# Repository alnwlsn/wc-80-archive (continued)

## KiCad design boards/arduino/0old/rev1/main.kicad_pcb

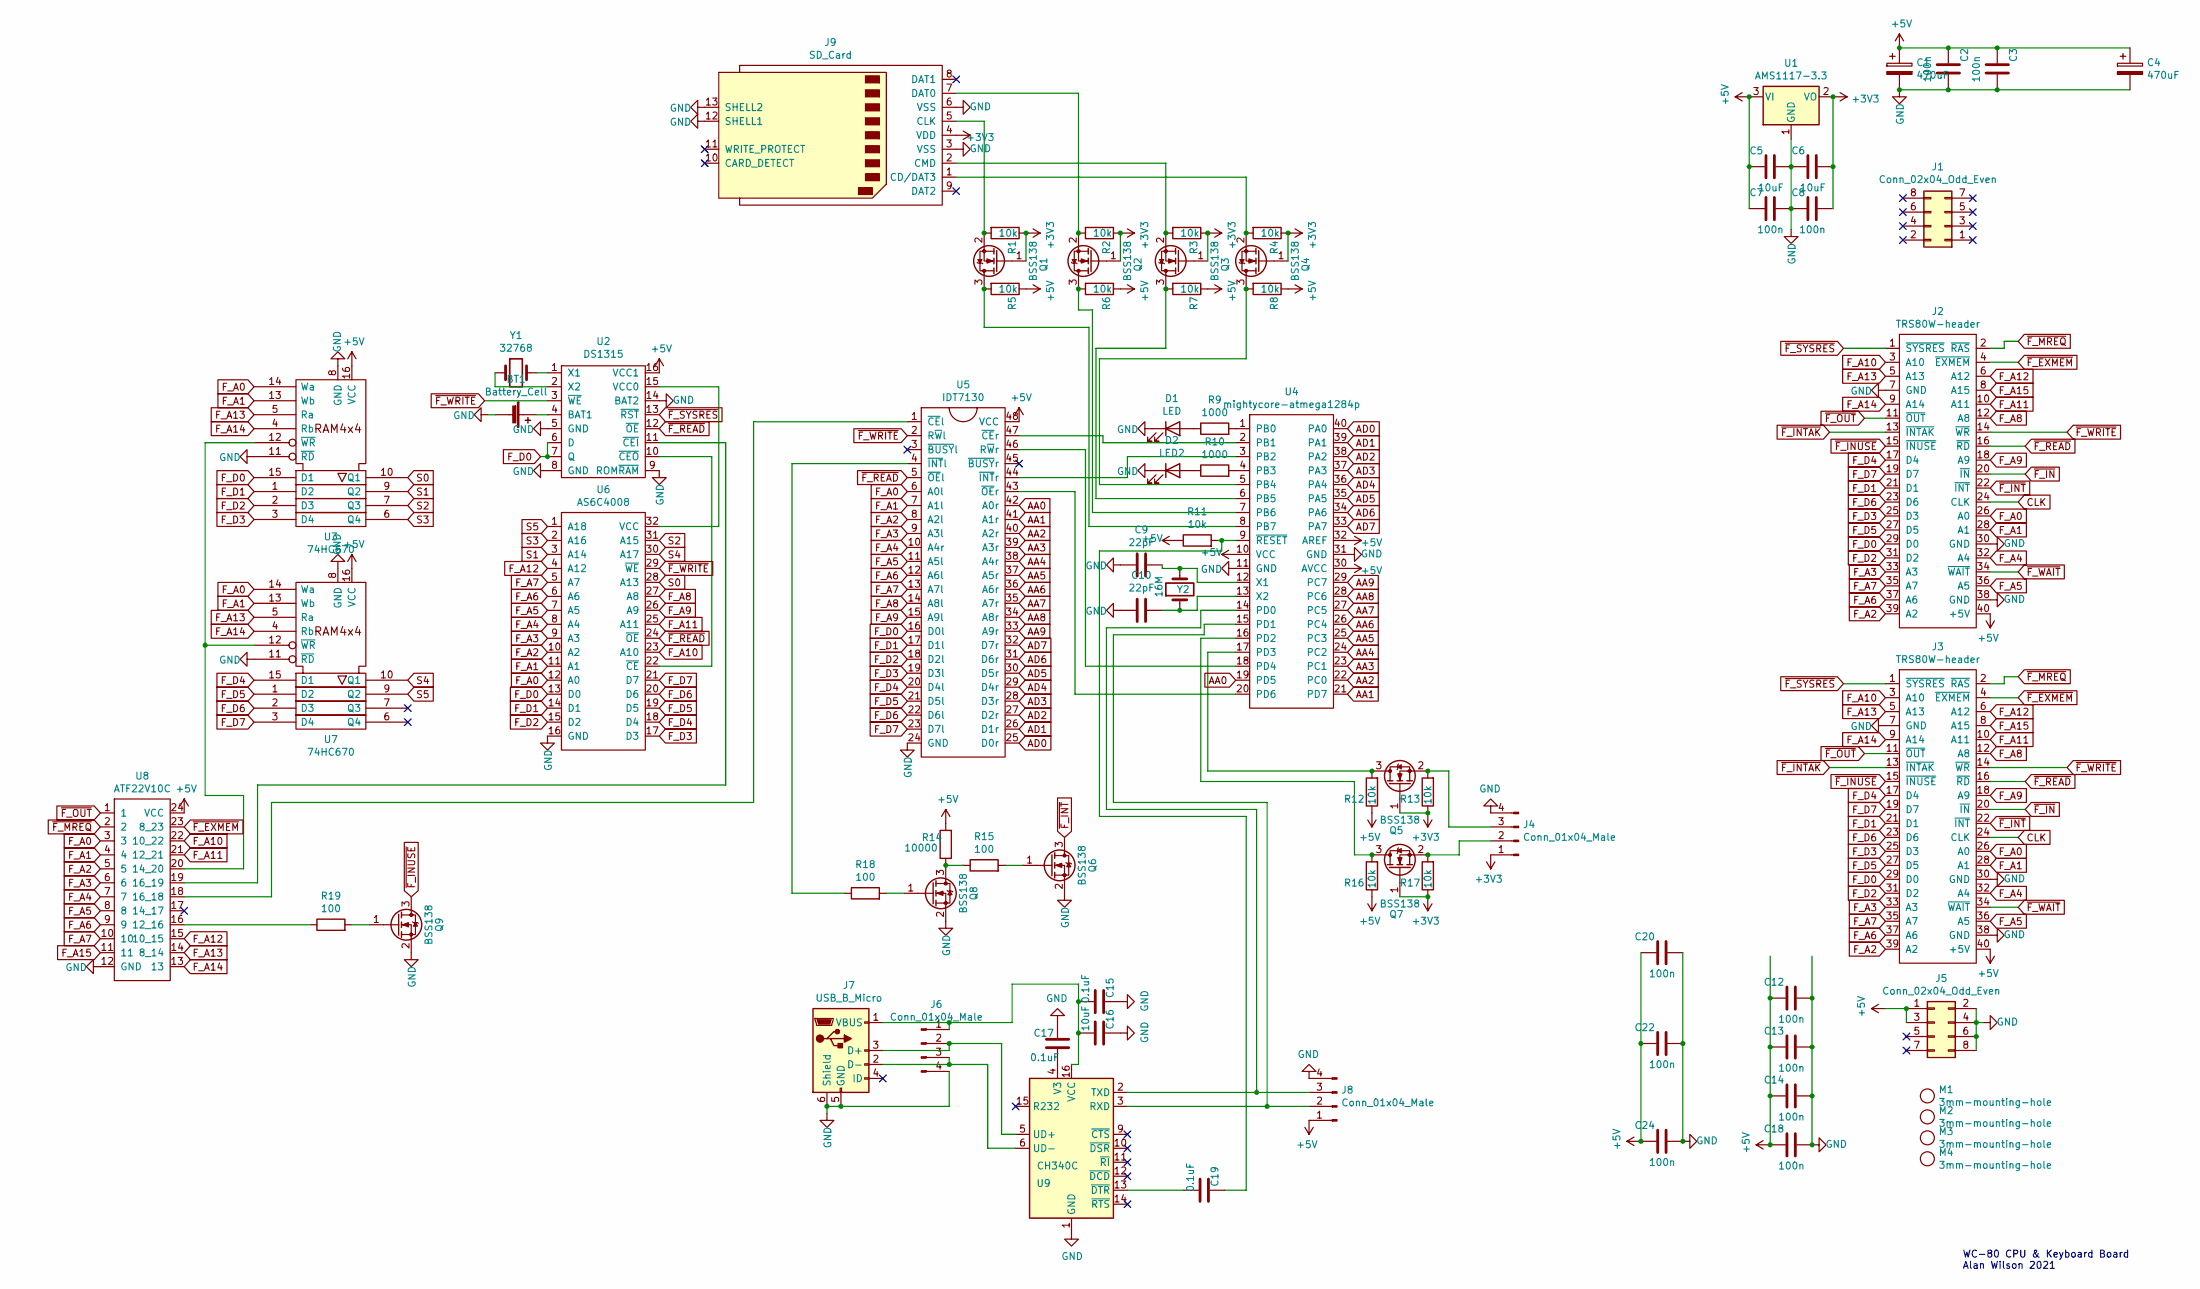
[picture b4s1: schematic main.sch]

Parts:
BT1: Battery_Cell; BS-01-A4CJ004
C1, C4: 470uF; CP_Radial_D8.0mm_P3.50mm
C2, C3, C7, C8, C12, C13, C14, C18, C20, C22, C24: 100n; C_0805_2012Metric
C5, C6, C16: 10uF; C_0805_2012Metric
C9, C10: 22pF; C_0805_2012Metric
C15, C17, C19: 0.1uF; C_0805_2012Metric
D1: LED; LED_D3.0mm
D2: LED2; LED_D3.0mm
J1, J5: Conn_02x04_Odd_Even; PinHeader_2x04_P2.54mm_Vertical
J2, J3: TRS80W-header; PinHeader_2x20_P2.54mm_Vertical
J4, J6, J8: Conn_01x04_Male; PinHeader_1x04_P2.54mm_Vertical
J7: USB_B_Micro; USB_Micro-B_Molex-105017-0001
J9: SD_Card; SD_Card_ XUNPU_SD-101
M1, M2, M3, M4: 3mm-mounting-hole; MountingHole_3.2mm_M3_DIN965
Q1, Q2, Q3, Q4, Q5, Q6, Q7, Q8, Q9: BSS138; SOT-23
R1, R2, R3, R4, R5, R6, R7, R8, R11, R12, R13, R16, R17: 10k; R_0805_2012Metric
R9, R10: 1000; R_0805_2012Metric
R14: 10000; R_0805_2012Metric
R15, R18, R19: 100; R_0805_2012Metric
U1: AMS1117-3.3; SOT-223-3_TabPin2
U2: DS1315; DIP-16_W7.62mm_Socket
U3, U7: 74HC670; DIP-16_W7.62mm_Socket
U4: mightycore-atmega1284p; DIP-40_W15.24mm_Socket
U5: IDT7130; DIP-48_W15.24mm_Socket
U6: AS6C4008; DIP-32_W15.24mm
U8: ATF22V10C; DIP-24_W7.62mm
U9: CH340C; SOIC-16_3.9x9.9mm_P1.27mm
Y1: 32768; Crystal_AT310_D3.0mm_L10.0mm_Horizontal
Y2: 16M; Crystal_HC49-U_Vertical

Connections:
+3V3: C6.2, C8.2, J4.1, J9.4 (VDD), Q1.1 (G), Q2.1 (G), Q3.1 (G), Q4.1 (G), Q5.1 (G), Q7.1 (G), R1.1, R2.1, R3.1, R4.1, R13.1, R17.1, U1.2 (VO)
+5V: C1.1, C2.1, C3.1, C4.1, C5.1, C7.1, C12.1, C13.1, C14.1, C18.1, C20.1, C22.1, C24.1, J2.40 (+5V), J3.40 (+5V), J5.1, J5.3, J8.1, R5.1, R6.1, R7.1, R8.1, R11.1, R12.1, R14.2, R16.1, U1.3 (VI), U2.16 (VCC1), U3.16 (VCC), U4.10 (VCC), U4.30 (AVCC), U4.32 (AREF), U5.48 (VCC), U7.16 (VCC), U8.24 (VCC)
AA0: U4.19 (PD5), U5.42 (A0r)
AA1: U4.21 (PD7), U5.41 (A1r)
AA2: U4.22 (PC0), U5.40 (A2r)
AA3: U4.23 (PC1), U5.39 (A3r)
AA4: U4.24 (PC2), U5.38 (A4r)
AA5: U4.25 (PC3), U5.37 (A5r)
AA6: U4.26 (PC4), U5.36 (A6r)
AA7: U4.27 (PC5), U5.35 (A7r)
AA8: U4.28 (PC6), U5.34 (A8r)
AA9: U4.29 (PC7), U5.33 (A9r)
AD0: U4.40 (PA0), U5.25 (D0r)
AD1: U4.39 (PA1), U5.26 (D1r)
AD2: U4.38 (PA2), U5.27 (D2r)
AD3: U4.37 (PA3), U5.28 (D3r)
AD4: U4.36 (PA4), U5.29 (D4r)
AD5: U4.35 (PA5), U5.30 (D5r)
AD6: U4.34 (PA6), U5.31 (D6r)
AD7: U4.33 (PA7), U5.32 (D7r)
CLK: J2.24 (CLK), J3.24 (CLK)
F_A0: J2.26 (A0), J3.26 (A0), U3.14 (Wa), U5.6 (A0l), U6.12 (A0), U7.14 (Wa), U8.3
F_A1: J2.28 (A1), J3.28 (A1), U3.13 (Wb), U5.7 (A1l), U6.11 (A1), U7.13 (Wb), U8.4
F_A2: J2.39 (A2), J3.39 (A2), U5.8 (A2l), U6.10 (A2), U8.5
F_A3: J2.33 (A3), J3.33 (A3), U5.9 (A3l), U6.9 (A3), U8.6
F_A4: J2.32 (A4), J3.32 (A4), U5.10 (A4r), U6.8 (A4), U8.7
F_A5: J2.36 (A5), J3.36 (A5), U5.11 (A5l), U6.7 (A5), U8.8
F_A6: J2.37 (A6), J3.37 (A6), U5.12 (A6l), U6.6 (A6), U8.9
F_A7: J2.35 (A7), J3.35 (A7), U5.13 (A7l), U6.5 (A7), U8.10
F_A8: J2.12 (A8), J3.12 (A8), U5.14 (A8l), U6.27 (A8)
F_A9: J2.18 (A9), J3.18 (A9), U5.15 (A9l), U6.26 (A9)
F_A10: J2.3 (A10), J3.3 (A10), U6.23 (A10), U8.22 (10_22)
F_A11: J2.10 (A11), J3.10 (A11), U6.25 (A11), U8.21 (12_21)
F_A12: J2.6 (A12), J3.6 (A12), U6.4 (A12), U8.15 (10_15)
F_A13: J2.5 (A13), J3.5 (A13), U3.5 (Ra), U7.5 (Ra), U8.14 (8_14)
F_A14: J2.9 (A14), J3.9 (A14), U3.4 (Rb), U7.4 (Rb), U8.13
F_A15: J2.8 (A15), J3.8 (A15), U8.11
F_D0: J2.29 (D0), J3.29 (D0), U2.6 (D), U2.7 (Q), U3.15 (D1), U5.16 (D0l), U6.13 (D0)
F_D1: J2.21 (D1), J3.21 (D1), U3.1 (D2), U5.17 (D1l), U6.14 (D1)
F_D2: J2.31 (D2), J3.31 (D2), U3.2 (D3), U5.18 (D2l), U6.15 (D2)
F_D3: J2.25 (D3), J3.25 (D3), U3.3 (D4), U5.19 (D3l), U6.17 (D3)
F_D4: J2.17 (D4), J3.17 (D4), U5.20 (D4l), U6.18 (D4), U7.15 (D1)
F_D5: J2.27 (D5), J3.27 (D5), U5.21 (D5l), U6.19 (D5), U7.1 (D2)
F_D6: J2.23 (D6), J3.23 (D6), U5.22 (D6l), U6.20 (D6), U7.2 (D3)
F_D7: J2.19 (D7), J3.19 (D7), U5.23 (D7l), U6.21 (D7), U7.3 (D4)
GND: BT1.2 (-), C1.2, C2.2, C3.2, C4.2, C5.2, C6.1, C7.2, C8.1, C9.2, C10.2, C12.2, C13.2, C14.2, C15.2, C16.2, C17.2, C18.2, C20.2, C22.2, C24.2, D1.1 (K), D2.1 (K), J2.7 (GND), J2.30 (GND), J2.38 (GND), J3.7 (GND), J3.30 (GND), J3.38 (GND), J4.4, J5.2, J5.4, J5.6, J5.8, J6.4, J7.5 (GND), J7.6 (Shield), J8.4, J9.3 (VSS), J9.6 (VSS), J9.12 (SHELL1), J9.13 (SHELL2), Q6.2 (S), Q8.2 (S), Q9.2 (S), U1.1 (GND), U2.5 (GND), U2.8 (GND), U2.9 (ROM~RAM~), U2.14 (BAT2), U3.8 (GND), U3.11 (~RD), U4.11 (GND), U4.31 (GND), U5.24 (GND), U6.16 (GND), U7.8 (GND), U7.11 (~RD), U8.12 (GND), U9.1 (GND)
unnamed: BT1.1 (+), U2.4 (BAT1)
unnamed: C9.1, U4.12 (X1), Y2.2
unnamed: C10.1, U4.13 (X2), Y2.1
unnamed: C15.1, C16.1, J6.1, J7.1 (VBUS), U9.16 (VCC)
unnamed: C17.1, U9.4 (V3)
unnamed: C19.1, U9.13 (~DTR)
unnamed: C19.2, R11.2, U4.9 (~RESET~)
unnamed: D1.2 (A), R9.1
unnamed: D2.2 (A), R10.1
unnamed: J4.2, Q7.2 (S), R17.2
unnamed: J4.3, Q5.2 (S), R13.2
unnamed: J6.2, J7.3 (D+), U9.5 (UD+)
unnamed: J6.3, J7.2 (D-), U9.6 (UD-)
unnamed: J8.2, U4.15 (PD1), U9.3 (RXD)
unnamed: J8.3, U4.14 (PD0), U9.2 (TXD)
unnamed: J9.1 (CD/DAT3), Q4.2 (S), R4.2
unnamed: J9.2 (CMD), Q3.2 (S), R3.2
unnamed: J9.5 (CLK), Q1.2 (S), R1.2
unnamed: J9.7 (DAT0), Q2.2 (S), R2.2
unnamed: Q1.3 (D), R5.2, U4.8 (PB7)
unnamed: Q2.3 (D), R6.2, U4.7 (PB6)
unnamed: Q3.3 (D), R7.2, U4.6 (PB5)
unnamed: Q4.3 (D), R8.2, U4.5 (PB4)
unnamed: Q5.3 (D), R12.2, U4.17 (PD3)
unnamed: Q6.1 (G), R15.2
unnamed: Q7.3 (D), R16.2, U4.16 (PD2)
unnamed: Q8.1 (G), R18.2
unnamed: Q8.3 (D), R14.1, R15.1
unnamed: Q9.1 (G), R19.2
unnamed: R9.2, U4.1 (PB0)
unnamed: R10.2, U4.4 (PB3)
unnamed: R18.1, U5.4 (~INT~l)
unnamed: R19.1, U8.16 (12_16)
unnamed: U2.1 (X1), Y1.2
unnamed: U2.2 (X2), Y1.1
unnamed: U2.10 (~CEO~), U6.22 (~CE~)
unnamed: U2.11 (~CEI~), U8.19 (16_19)
unnamed: U2.15 (VCC0), U6.32 (VCC)
unnamed: U3.12 (~WR), U7.12 (~WR), U8.20 (14_20)
unnamed: U4.2 (PB1), U5.47 (~CE~r)
unnamed: U4.3 (PB2), U5.44 (~INT~r)
unnamed: U4.18 (PD4), U5.46 (R~W~r)
unnamed: U4.20 (PD6), U5.43 (~OE~r)
unnamed: U5.1 (~CE~l), U8.18 (16_18)
S0: U3.10 (Q1), U6.28 (A13)
S1: U3.9 (Q2), U6.3 (A14)
S2: U3.7 (Q3), U6.31 (A15)
S3: U3.6 (Q4), U6.2 (A16)
S4: U6.30 (A17), U7.10 (Q1)
S5: U6.1 (A18), U7.9 (Q2)
~F_EXMEM~: J2.4 (~EXMEM~), J3.4 (~EXMEM~), U8.23 (8_23)
~F_INTAK~: J2.13 (~INTAK~), J3.13 (~INTAK~)
~F_INT~: J2.22 (~INT~), J3.22 (~INT~), Q6.3 (D)
~F_INUSE~: J2.15 (~INUSE~), J3.15 (~INUSE~), Q9.3 (D)
~F_IN~: J2.20 (~IN~), J3.20 (~IN~)
~F_MREQ~: J2.2 (~RAS~), J3.2 (~RAS~), U8.2
~F_OUT~: J2.11 (~OUT~), J3.11 (~OUT~), U8.1
~F_READ~: J2.16 (~RD~), J3.16 (~RD~), U2.12 (~OE~), U5.5 (~OE~l), U6.24 (~OE~)
~F_SYSRES~: J2.1 (~SYSRES~), J3.1 (~SYSRES~), U2.13 (~RST~)
~F_WAIT~: J2.34 (~WAIT~), J3.34 (~WAIT~)
~F_WRITE~: J2.14 (~WR~), J3.14 (~WR~), U2.3 (~WE~), U5.2 (R~W~l), U6.29 (~WE~)

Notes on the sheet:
WC-80 CPU & Keyboard Board Alan Wilson 2021

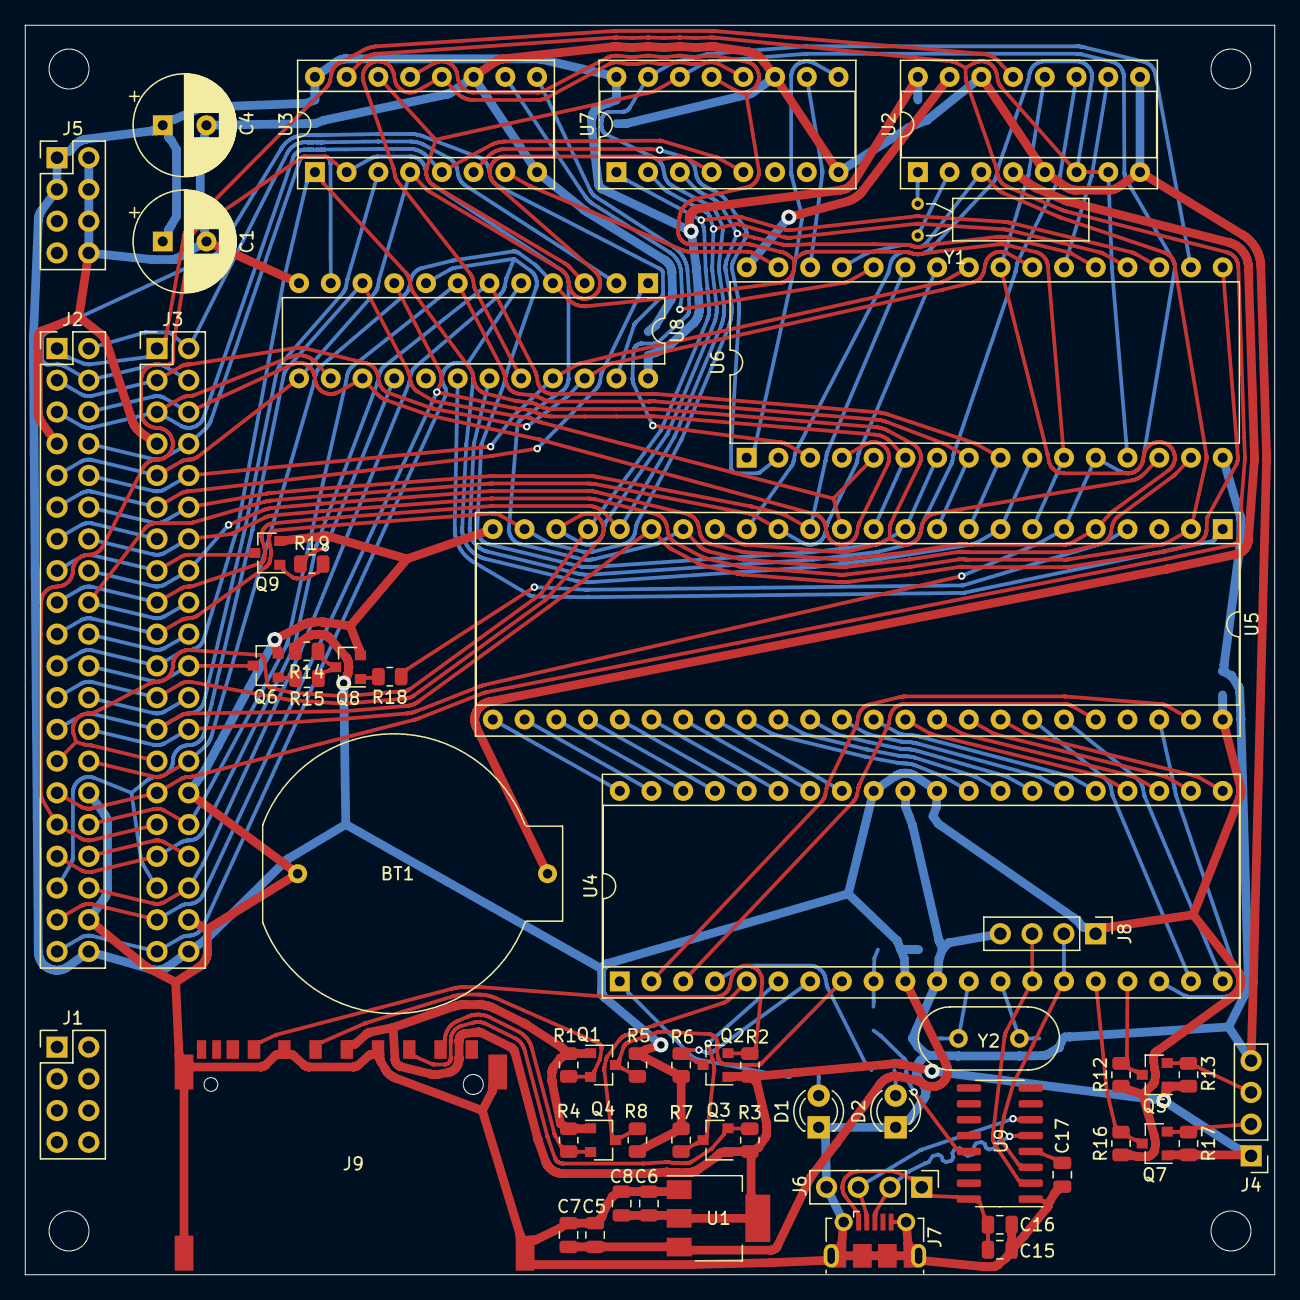
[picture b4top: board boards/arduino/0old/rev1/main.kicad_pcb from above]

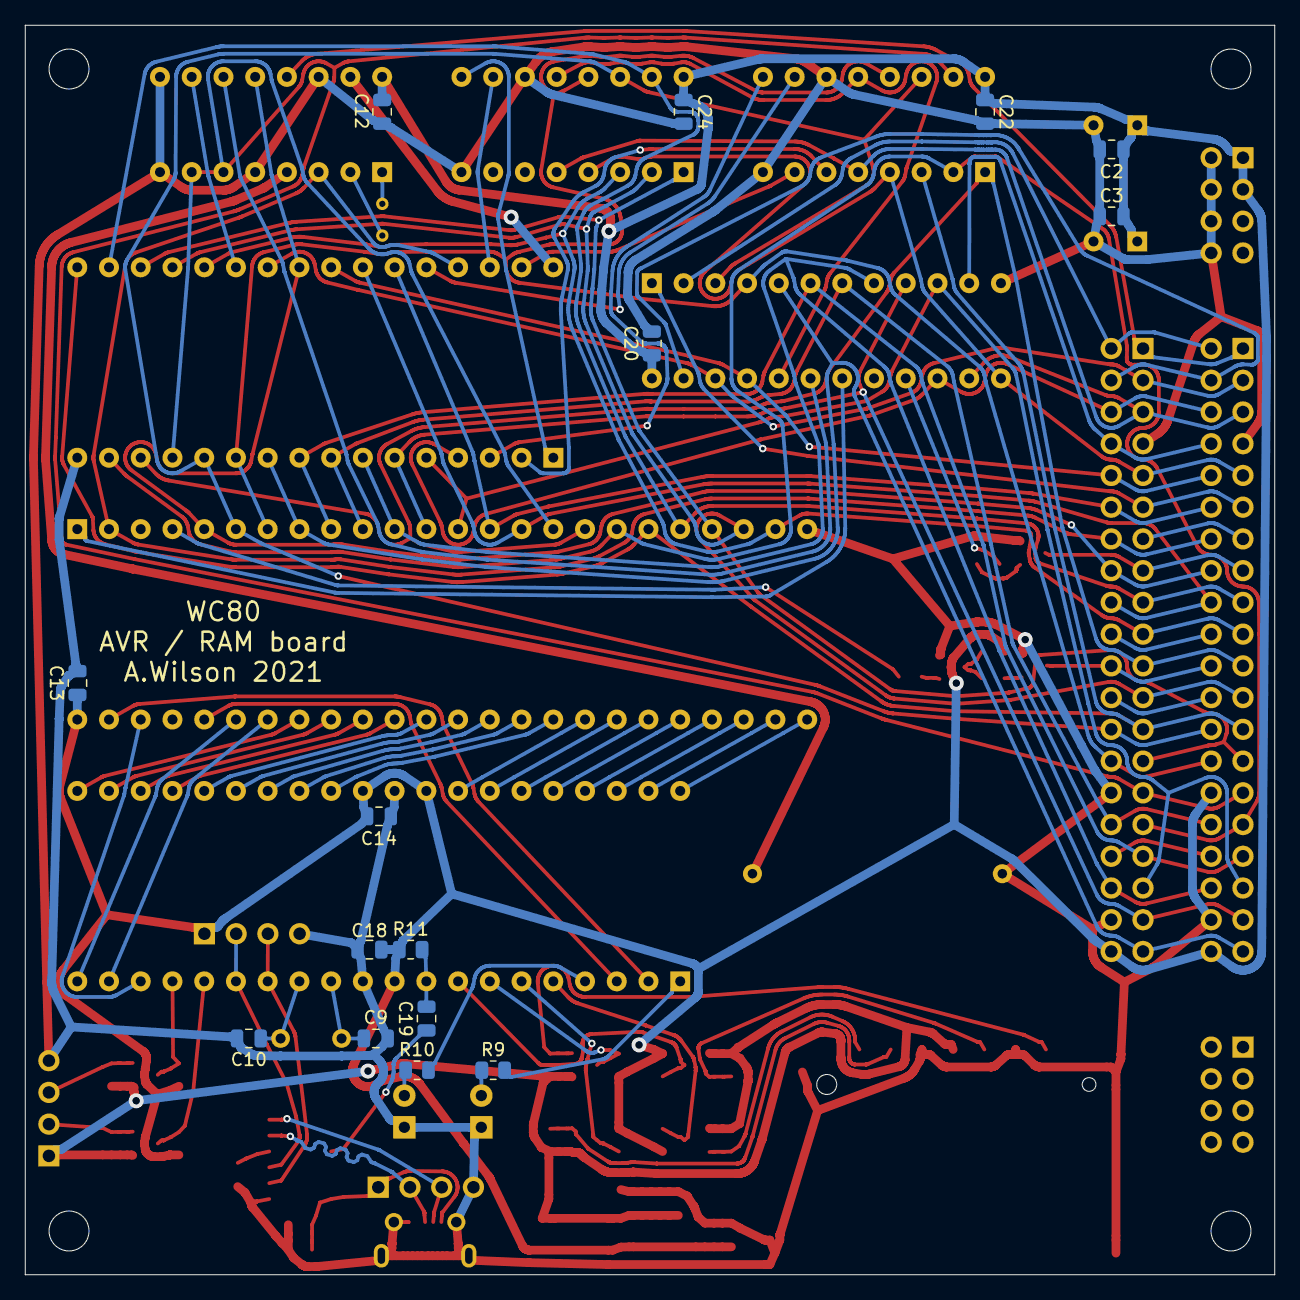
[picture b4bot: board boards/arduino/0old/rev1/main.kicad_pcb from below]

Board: 2 copper layers, 100.0 x 100.0 mm, 76 parts (15 on the bottom side), 107 nets.

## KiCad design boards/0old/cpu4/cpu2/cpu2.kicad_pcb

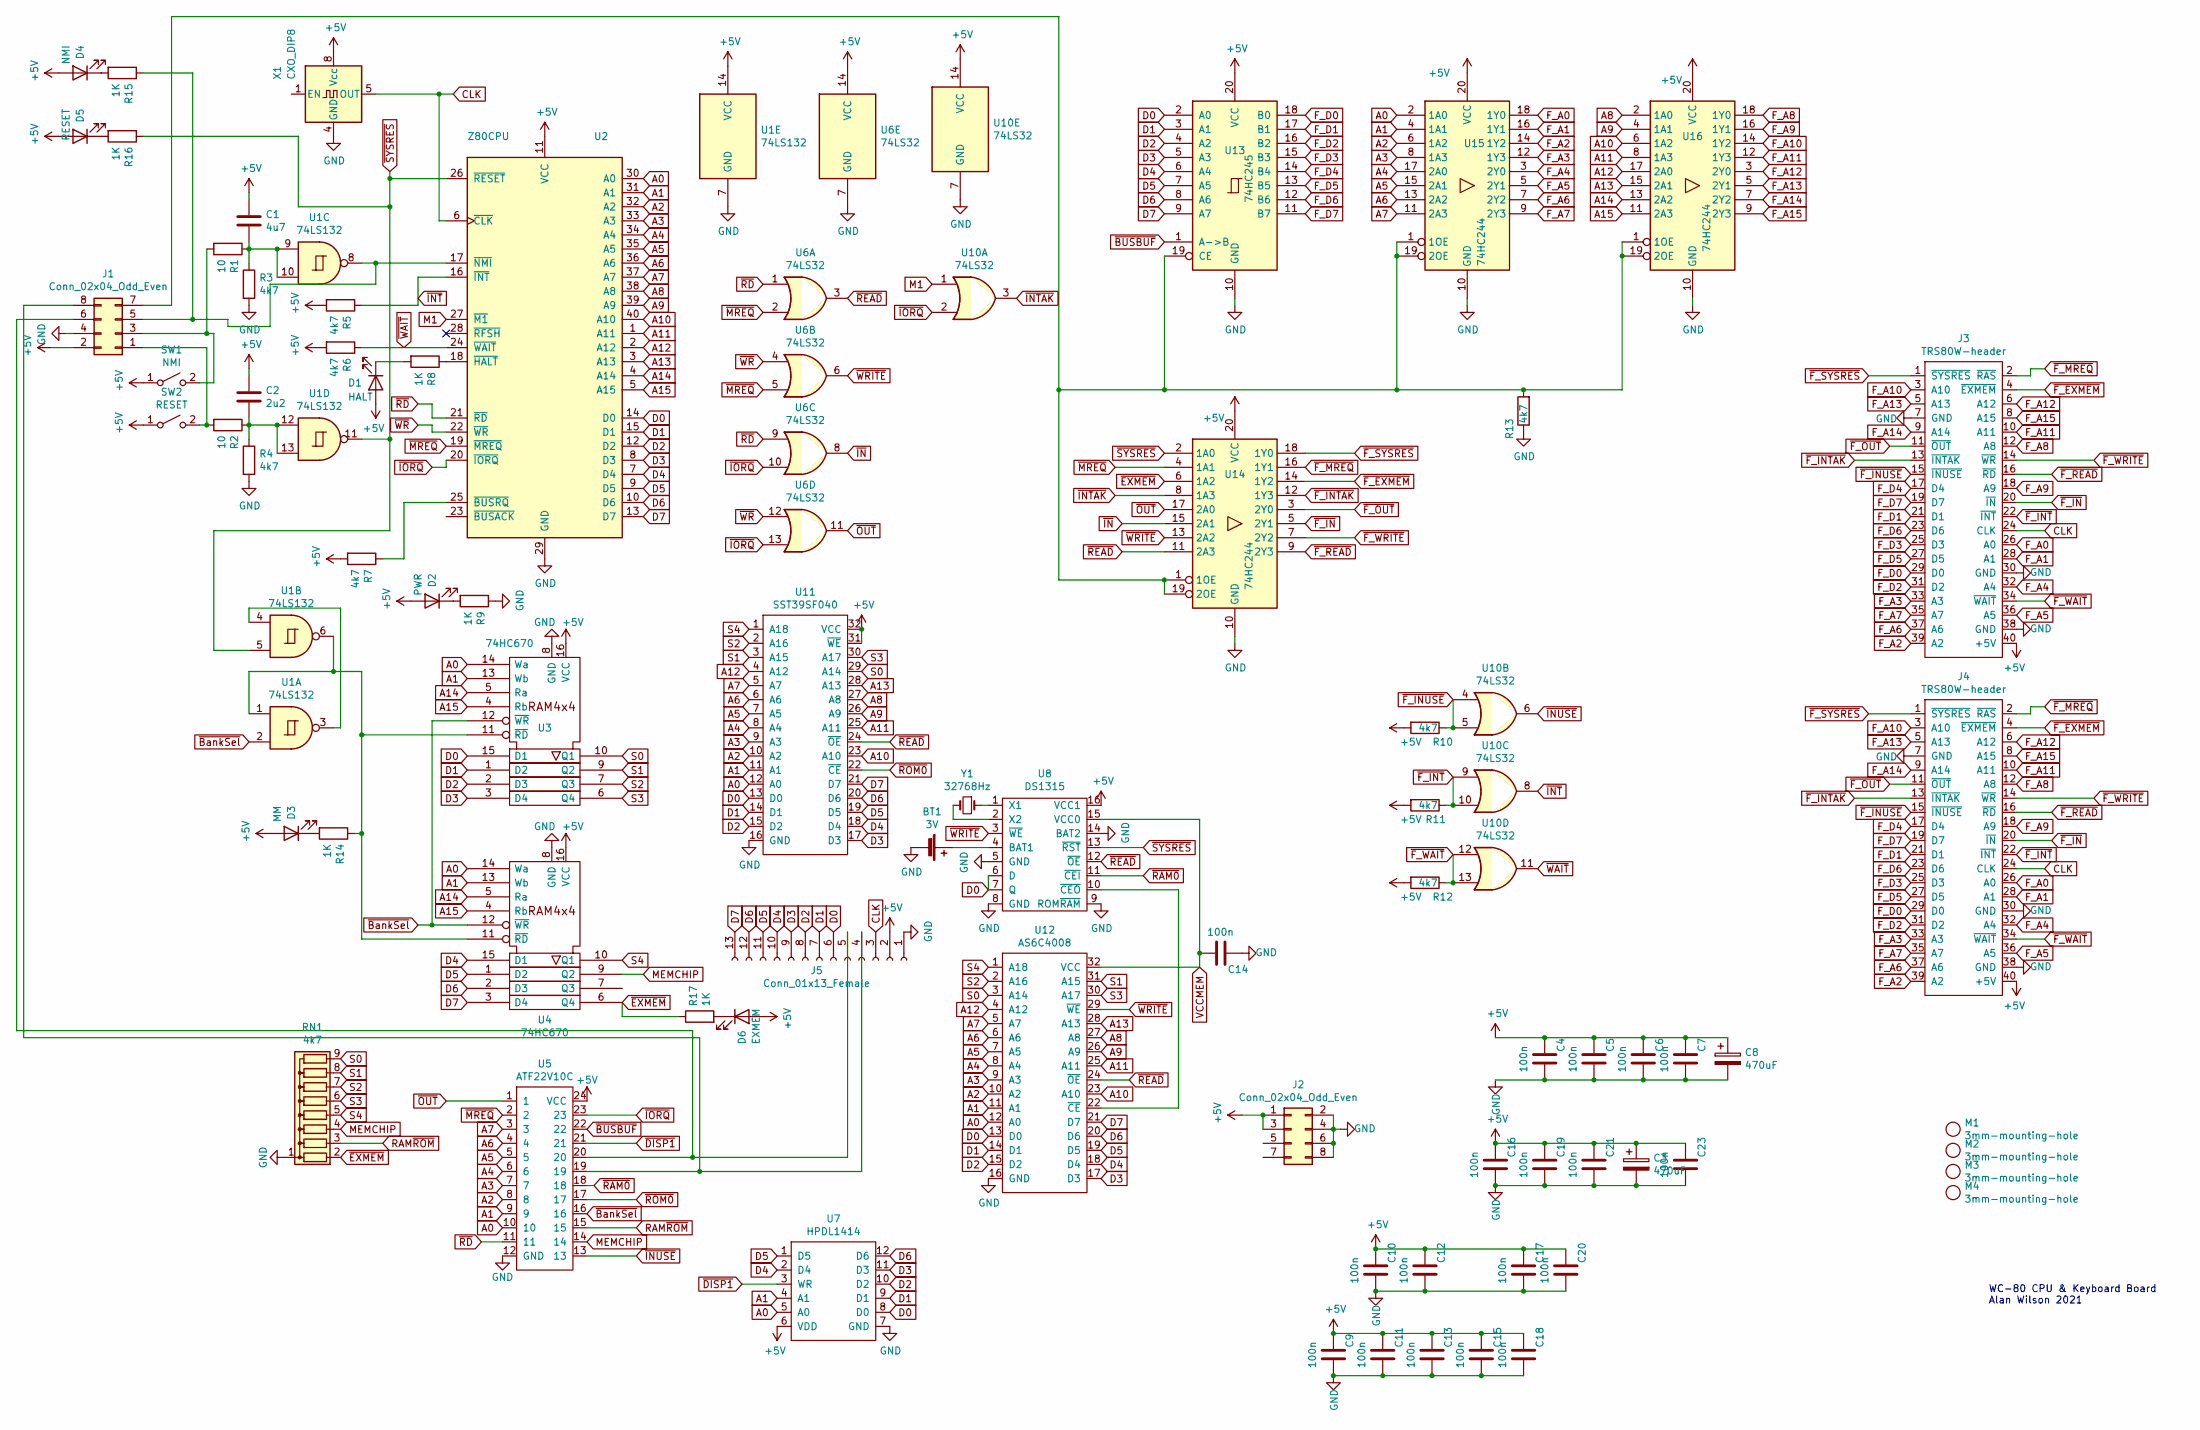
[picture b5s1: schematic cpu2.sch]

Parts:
BT1: 3V; BS-01-A4CJ004
C1: 4u7; C_0805_2012Metric
C2: 2u2; C_0805_2012Metric
C3, C8: 470uF; CP_Radial_D8.0mm_P3.50mm
C4, C5, C6, C7, C9, C10, C11, C12, C13, C14, C15, C16, C17, C18, C19, C20, C21, C23: 100n; C_0805_2012Metric
D1: HALT; LED_D3.0mm_FlatTop
D2: PWR; LED_D3.0mm_FlatTop
D3: MM; LED_D3.0mm_FlatTop
D4: NMI; LED_D3.0mm_FlatTop
D5: RESET; LED_D3.0mm_FlatTop
D6: EXMEM; LED_D3.0mm_FlatTop
J1, J2: Conn_02x04_Odd_Even; PinHeader_2x04_P2.54mm_Vertical
J3, J4: TRS80W-header; PinHeader_2x20_P2.54mm_Vertical
J5: Conn_01x13_Female; PinHeader_1x13_P2.54mm_Vertical
M1, M2, M3, M4: 3mm-mounting-hole; MountingHole_3.2mm_M3_DIN965_Pad
R1, R2: 10; R_0805_2012Metric
R3, R4, R5, R6, R7, R10, R11, R12, R13: 4k7; R_0805_2012Metric
R8, R9, R14, R15, R16, R17: 1K; R_0805_2012Metric
RN1: 4k7; R_Array_SIP9
SW1: NMI; SW_PUSH_6mm
SW2: RESET; SW_PUSH_6mm
U1: 74LS132; DIP-14_W7.62mm_Socket
U2: Z80CPU; DIP-40_W15.24mm_Socket
U3, U4: 74HC670; DIP-16_W7.62mm_Socket
U5: ATF22V10C; DIP-24_W7.62mm_Socket
U6, U10: 74LS32; DIP-14_W7.62mm_Socket
U7: HPDL1414; DIP-24_W15.24mm_Socket
U8: DS1315; DIP-16_W7.62mm_Socket
U11: SST39SF040; DIP-32_W15.24mm_Socket
U12: AS6C4008; DIP-32_W15.24mm_Socket
U13: 74HC245; DIP-20_W7.62mm_Socket
U14, U15, U16: 74HC244; DIP-20_W7.62mm_Socket
X1: CXO_DIP8; Oscillator_DIP-8
Y1: 32768Hz; Crystal_AT310_D3.0mm_L10.0mm_Horizontal

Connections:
+5V: C1.1, C2.1, C3.1, C4.1, C5.1, C6.1, C7.1, C8.1, C9.1, C10.1, C11.1, C12.1, C13.1, C15.1, C16.1, C17.1, C18.1, C19.1, C20.1, C21.1, C23.1, D1.2 (A), D2.2 (A), D3.2 (A), D4.2 (A), D5.2 (A), D6.2 (A), J1.2, J2.1, J2.3, J3.40 (+5V), J4.40 (+5V), J5.2, R5.2, R6.2, R7.2, R10.2, R11.2, R12.2, SW1.1 (A), SW2.1 (A), U1.14 (VCC), U2.11 (VCC), U3.16 (VCC), U4.16 (VCC), U5.24 (VCC), U6.14 (VCC), U7.6 (VDD), U8.16 (VCC1), U10.14 (VCC), U11.31 (~WE~), U11.32 (VCC), U13.20 (VCC), U14.20 (VCC), U15.20 (VCC), U16.20 (VCC), X1.8 (Vcc)
A0: U2.30 (A0), U3.14 (Wa), U4.14 (Wa), U5.10, U7.5 (A0), U11.12 (A0), U12.12 (A0), U15.2 (1A0)
A1: U2.31 (A1), U3.13 (Wb), U4.13 (Wb), U5.9, U7.4 (A1), U11.11 (A1), U12.11 (A1), U15.4 (1A1)
A2: U2.32 (A2), U5.8, U11.10 (A2), U12.10 (A2), U15.6 (1A2)
A3: U2.33 (A3), U5.7, U11.9 (A3), U12.9 (A3), U15.8 (1A3)
A4: U2.34 (A4), U5.6, U11.8 (A4), U12.8 (A4), U15.17 (2A0)
A5: U2.35 (A5), U5.5, U11.7 (A5), U12.7 (A5), U15.15 (2A1)
A6: U2.36 (A6), U5.4, U11.6 (A6), U12.6 (A6), U15.13 (2A2)
A7: U2.37 (A7), U5.3, U11.5 (A7), U12.5 (A7), U15.11 (2A3)
A8: U2.38 (A8), U11.27 (A8), U12.27 (A8), U16.2 (1A0)
A9: U2.39 (A9), U11.26 (A9), U12.26 (A9), U16.4 (1A1)
A10: U2.40 (A10), U11.23 (A10), U12.23 (A10), U16.6 (1A2)
A11: U2.1 (A11), U11.25 (A11), U12.25 (A11), U16.8 (1A3)
A12: U2.2 (A12), U11.4 (A12), U12.4 (A12), U16.17 (2A0)
A13: U2.3 (A13), U11.28 (A13), U12.28 (A13), U16.15 (2A1)
A14: U2.4 (A14), U3.5 (Ra), U4.5 (Ra), U16.13 (2A2)
A15: U2.5 (A15), U3.4 (Rb), U4.4 (Rb), U16.11 (2A3)
CLK: J3.24 (CLK), J4.24 (CLK), J5.3, U2.6 (~CLK~), X1.5 (OUT)
D0: J5.6, U2.14 (D0), U3.15 (D1), U7.8 (D0), U8.6 (D), U8.7 (Q), U11.13 (D0), U12.13 (D0), U13.2 (A0)
D1: J5.7, U2.15 (D1), U3.1 (D2), U7.9 (D1), U11.14 (D1), U12.14 (D1), U13.3 (A1)
D2: J5.8, U2.12 (D2), U3.2 (D3), U7.10 (D2), U11.15 (D2), U12.15 (D2), U13.4 (A2)
D3: J5.9, U2.8 (D3), U3.3 (D4), U7.11 (D3), U11.17 (D3), U12.17 (D3), U13.5 (A3)
D4: J5.10, U2.7 (D4), U4.15 (D1), U7.2 (D4), U11.18 (D4), U12.18 (D4), U13.6 (A4)
D5: J5.11, U2.9 (D5), U4.1 (D2), U7.1 (D5), U11.19 (D5), U12.19 (D5), U13.7 (A5)
D6: J5.12, U2.10 (D6), U4.2 (D3), U7.12 (D6), U11.20 (D6), U12.20 (D6), U13.8 (A6)
D7: J5.13, U2.13 (D7), U4.3 (D4), U11.21 (D7), U12.21 (D7), U13.9 (A7)
F_A0: J3.26 (A0), J4.26 (A0), U15.18 (1Y0)
F_A1: J3.28 (A1), J4.28 (A1), U15.16 (1Y1)
F_A2: J3.39 (A2), J4.39 (A2), U15.14 (1Y2)
F_A3: J3.33 (A3), J4.33 (A3), U15.12 (1Y3)
F_A4: J3.32 (A4), J4.32 (A4), U15.3 (2Y0)
F_A5: J3.36 (A5), J4.36 (A5), U15.5 (2Y1)
F_A6: J3.37 (A6), J4.37 (A6), U15.7 (2Y2)
F_A7: J3.35 (A7), J4.35 (A7), U15.9 (2Y3)
F_A8: J3.12 (A8), J4.12 (A8), U16.18 (1Y0)
F_A9: J3.18 (A9), J4.18 (A9), U16.16 (1Y1)
F_A10: J3.3 (A10), J4.3 (A10), U16.14 (1Y2)
F_A11: J3.10 (A11), J4.10 (A11), U16.12 (1Y3)
F_A12: J3.6 (A12), J4.6 (A12), U16.3 (2Y0)
F_A13: J3.5 (A13), J4.5 (A13), U16.5 (2Y1)
F_A14: J3.9 (A14), J4.9 (A14), U16.7 (2Y2)
F_A15: J3.8 (A15), J4.8 (A15), U16.9 (2Y3)
F_D0: J3.29 (D0), J4.29 (D0), U13.18 (B0)
F_D1: J3.21 (D1), J4.21 (D1), U13.17 (B1)
F_D2: J3.31 (D2), J4.31 (D2), U13.16 (B2)
F_D3: J3.25 (D3), J4.25 (D3), U13.15 (B3)
F_D4: J3.17 (D4), J4.17 (D4), U13.14 (B4)
F_D5: J3.27 (D5), J4.27 (D5), U13.13 (B5)
F_D6: J3.23 (D6), J4.23 (D6), U13.12 (B6)
F_D7: J3.19 (D7), J4.19 (D7), U13.11 (B7)
GND: BT1.2 (-), C3.2, C4.2, C5.2, C6.2, C7.2, C8.2, C9.2, C10.2, C11.2, C12.2, C13.2, C14.1, C15.2, C16.2, C17.2, C18.2, C19.2, C20.2, C21.2, C23.2, J1.4, J2.2, J2.4, J2.6, J2.8, J3.7 (GND), J3.30 (GND), J3.38 (GND), J4.7 (GND), J4.30 (GND), J4.38 (GND), J5.1, R3.2, R4.2, R9.1, R13.1, RN1.1 (common), U1.7 (GND), U2.29 (GND), U3.8 (GND), U4.8 (GND), U5.12 (GND), U6.7 (GND), U7.7 (GND), U8.5 (GND), U8.8 (GND), U8.9 (ROM~RAM~), U8.14 (BAT2), U10.7 (GND), U11.16 (GND), U12.16 (GND), U13.10 (GND), U14.10 (GND), U15.10 (GND), U16.10 (GND), X1.4 (GND)
M1: U2.27 (~M1~), U10.1
MEMCHIP: RN1.4 (R3), U4.9 (Q2), U5.14
unnamed: BT1.1 (+), U8.4 (BAT1)
unnamed: C1.2, R1.1, R3.1, U1.9, U1.10
unnamed: C2.2, R2.1, R4.1, U1.12, U1.13
unnamed: D1.1 (K), R8.2
unnamed: D2.1 (K), R9.2
unnamed: D3.1 (K), R14.2
unnamed: D4.1 (K), R15.2
unnamed: D5.1 (K), R16.2
unnamed: D6.1 (K), R17.2
unnamed: J1.1, R2.2, SW2.2 (B)
unnamed: J1.3, R1.2, SW1.2 (B)
unnamed: J1.5, R15.1, U1.8, U2.17 (~NMI~)
unnamed: J1.6, J5.5, U5.20
unnamed: J1.7, R13.2, U13.19 (CE), U14.1 (1OE), U14.19 (2OE), U15.1 (1OE), U15.19 (2OE), U16.1 (1OE), U16.19 (2OE)
unnamed: J1.8, J5.4, U5.19
unnamed: R7.1, U2.25 (~BUSRQ~)
unnamed: R8.1, U2.18 (~HALT~)
unnamed: R14.1, U1.1, U1.6, U3.11 (~RD), U4.11 (~RD)
unnamed: U1.3, U1.4
unnamed: U8.1 (X1), Y1.1
unnamed: U8.2 (X2), Y1.2
unnamed: U8.10 (~CEO~), U12.22 (~CE~)
RAM~ROM~: RN1.3 (R2), U5.15
S0: RN1.9 (R8), U3.10 (Q1), U11.29 (A14), U12.3 (A14)
S1: RN1.8 (R7), U3.9 (Q2), U11.3 (A15), U12.31 (A15)
S2: RN1.7 (R6), U3.7 (Q3), U11.2 (A16), U12.2 (A16)
S3: RN1.6 (R5), U3.6 (Q4), U11.30 (A17), U12.30 (A17)
S4: RN1.5 (R4), U4.10 (Q1), U11.1 (A18), U12.1 (A18)
VCCMEM: C14.2, U8.15 (VCC0), U12.32 (VCC)
~BUSBUF~: U5.22, U13.1 (A->B)
~BankSel~: U1.2, U3.12 (~WR), U4.12 (~WR), U5.16
~DISP1~: U5.21, U7.3 (WR)
~EXMEM~: R17.1, RN1.2 (R1), U4.6 (Q4), U14.6 (1A2)
~F_EXMEM~: J3.4 (~EXMEM~), J4.4 (~EXMEM~), U14.14 (1Y2)
~F_INTAK~: J3.13 (~INTAK~), J4.13 (~INTAK~), U14.12 (1Y3)
~F_INT~: J3.22 (~INT~), J4.22 (~INT~), R11.1, U10.9, U10.10
~F_INUSE~: J3.15 (~INUSE~), J4.15 (~INUSE~), R10.1, U10.4, U10.5
~F_IN~: J3.20 (~IN~), J4.20 (~IN~), U14.5 (2Y1)
~F_MREQ~: J3.2 (~RAS~), J4.2 (~RAS~), U14.16 (1Y1)
~F_OUT~: J3.11 (~OUT~), J4.11 (~OUT~), U14.3 (2Y0)
~F_READ~: J3.16 (~RD~), J4.16 (~RD~), U14.9 (2Y3)
~F_SYSRES~: J3.1 (~SYSRES~), J4.1 (~SYSRES~), U14.18 (1Y0)
~F_WAIT~: J3.34 (~WAIT~), J4.34 (~WAIT~), R12.1, U10.12, U10.13
~F_WRITE~: J3.14 (~WR~), J4.14 (~WR~), U14.7 (2Y2)
~INTAK~: U10.3, U14.8 (1A3)
~INT~: R5.1, U2.16 (~INT~), U10.8
~INUSE~: U5.13, U10.6
~IN~: U6.8, U14.15 (2A1)
~IORQ~: U2.20 (~IORQ~), U5.23, U6.10, U6.13, U10.2
~MREQ~: U2.19 (~MREQ~), U5.2, U6.2, U6.5, U14.4 (1A1)
~OUT~: U5.1, U6.11, U14.17 (2A0)
~RAM0~: U5.18, U8.11 (~CEI~)
~RD~: U2.21 (~RD~), U5.11, U6.1, U6.9
~READ~: U6.3, U8.12 (~OE~), U11.24 (~OE~), U12.24 (~OE~), U14.11 (2A3)
~ROM0~: U5.17, U11.22 (~CE~)
~SYSRES~: R16.1, U1.5, U1.11, U2.26 (~RESET~), U8.13 (~RST~), U14.2 (1A0)
~WAIT~: R6.1, U2.24 (~WAIT~), U10.11
~WRITE~: U6.6, U8.3 (~WE~), U12.29 (~WE~), U14.13 (2A2)
~WR~: U2.22 (~WR~), U6.4, U6.12

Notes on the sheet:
WC-80 CPU & Keyboard Board Alan Wilson 2021

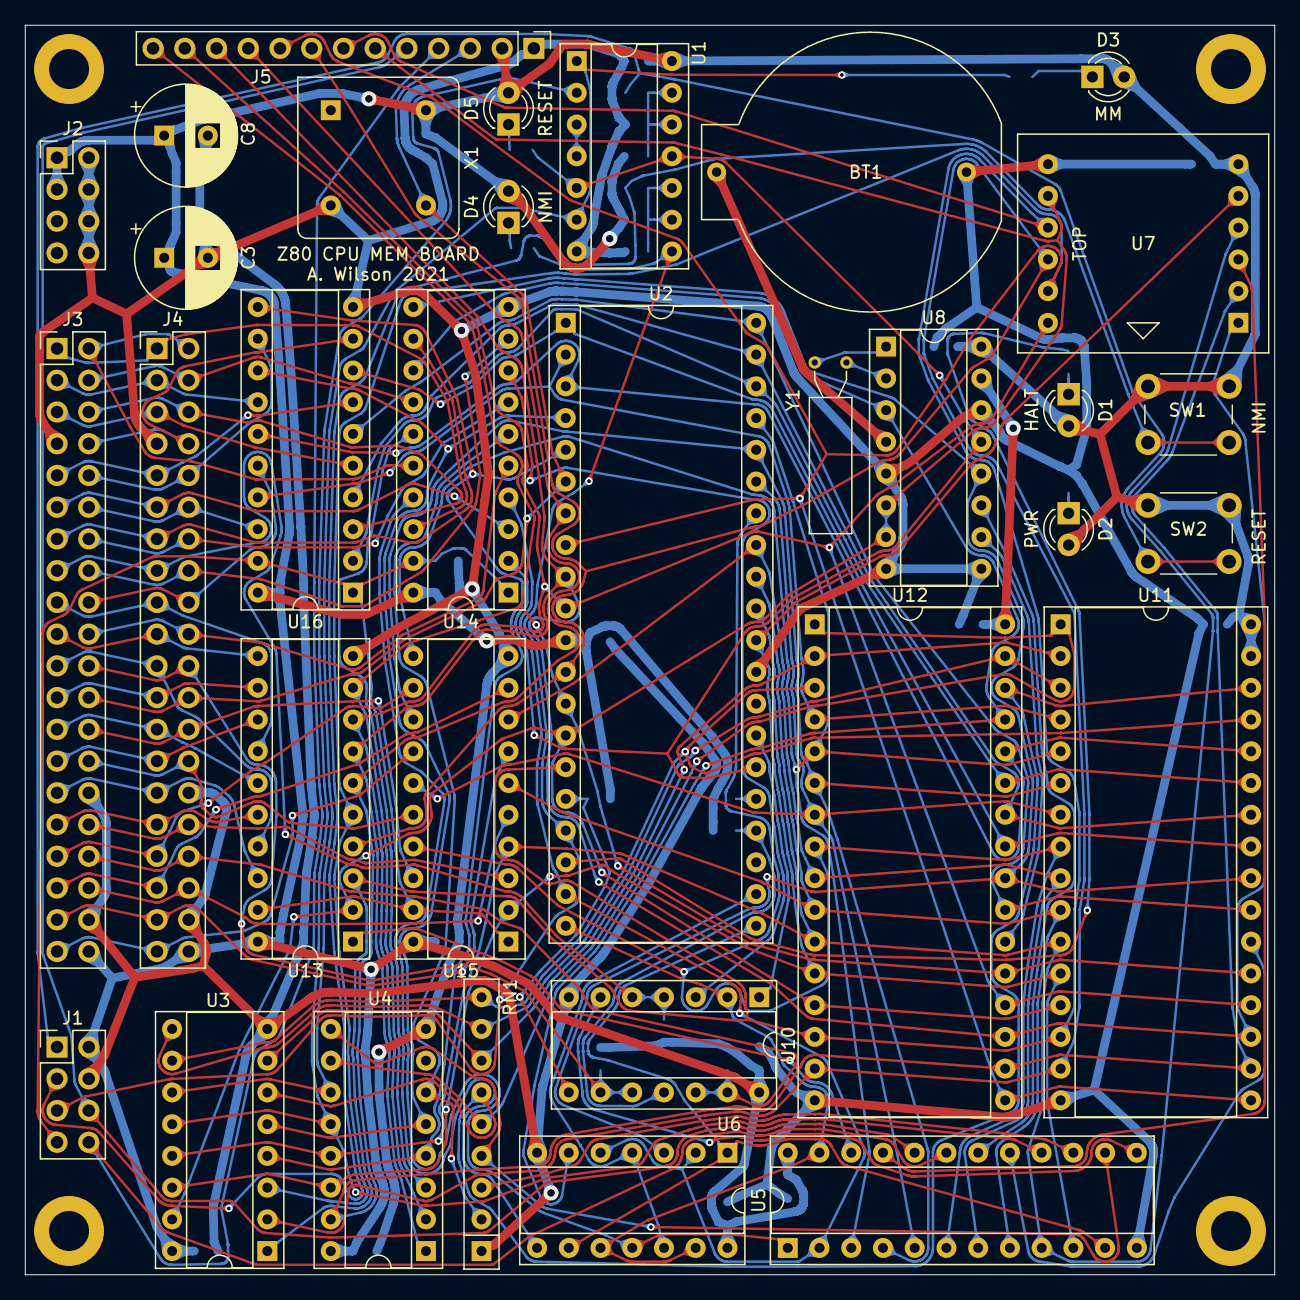
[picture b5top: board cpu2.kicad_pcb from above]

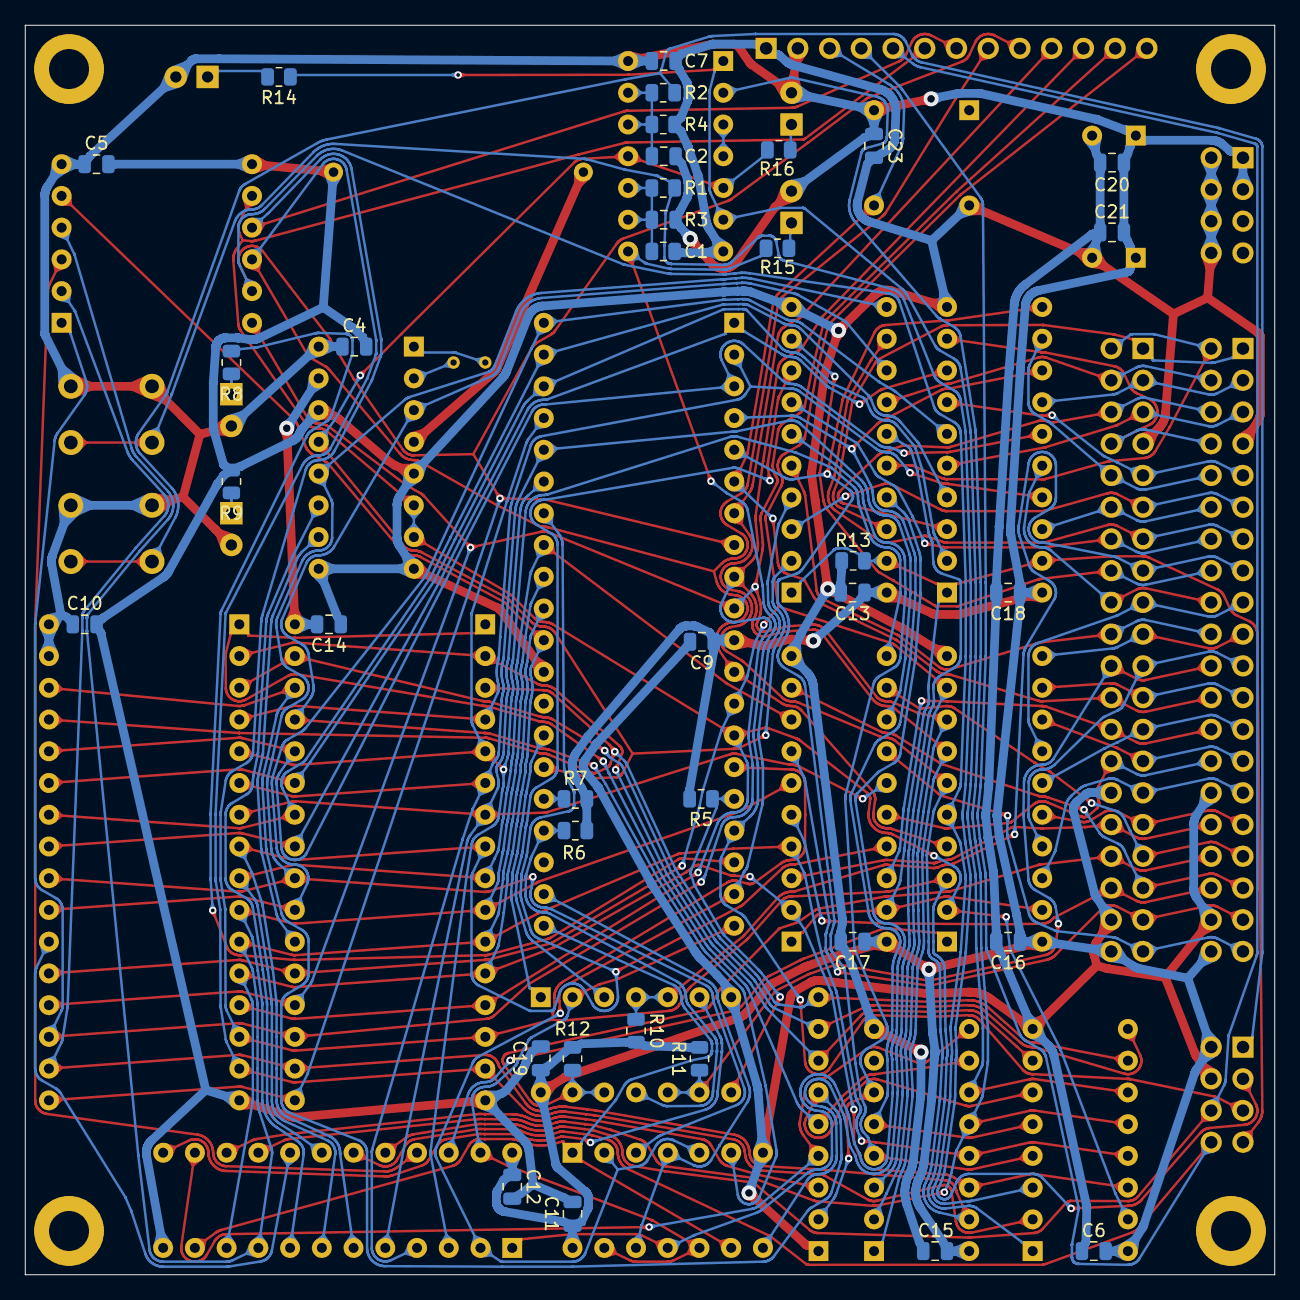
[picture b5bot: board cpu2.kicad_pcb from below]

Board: 2 copper layers, 100.0 x 100.0 mm, 73 parts (36 on the bottom side), 111 nets.
